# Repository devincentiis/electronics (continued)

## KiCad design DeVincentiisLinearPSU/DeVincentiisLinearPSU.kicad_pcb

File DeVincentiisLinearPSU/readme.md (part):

DIGITAL LINEAR POWER SUPPLY
=====================================

**PROJECT DESCRIPTION**

Electronics enthusiasts who want to try their hand at self-building a digital linear power supply for a small laboratory can create this device which in a single PCB brings together the essential functions to have a truly useful instrument.  
Taking inspiration from some circuit solutions of linear power supplies created in the past and available on the internet, this digitized model was conceived with microcontroller, DAC, LCD display and a single rotary encoder for interaction with the user.  
The objective is to be used with double winding 12-24 Vac transformers and a power of up to approximately 80VA capable of generating output voltages from 0 to 24 volts and currents from 0 to 3 amperes.  
With appropriate modifications the circuit could be scaled in both current and voltage. As it is it also accepts transformers with slightly different voltages, for example 15-30 or 10-20 Vac. At boot, the voltage supplied by the transformer is checked to set the maximum selectable via the rotary encoder and the possible presence of an intermediate socket.  
The power supply and the program also allow the use of single output transformers, at start-up the lack of the central socket is detected and indicated on the display and everything will continue to function regularly, however, it must be kept in mind that when we ask for supplies with high currents at low voltages, the two power transistors will have to dissipate a lot of heat and will force us to equip them with important heat sinks for cooling with forced ventilation.  
With a double winding transformer, however, the problem is halved as below the median voltage (also detected at switch-on) the relay will automatically switch to draw energy from the central tap of the transformer.  
The performance will never be the same as a modern switching power supply, but it will not be noisy. As you know, the operating principle is several decades old but is still considered valid in the laboratory where it is more likely to have problems with noise rather than heat.  
It can also be seen as a circuit to be connected to a transformer that has been in stock for many years and has never been used. In **Picture1** you can see one of the first creation placed into old media-center enclosure.

The firmware and wiring diagram are open source so they can be modified, resized, patched.  
An important improvement would be to replace the micro with an [STM32](http://www.st.com/en/microcontrollers-microprocessors/stm32f103ze.html) in the versions with two 12bit DACs, the considerable computing power would also [allow it to manage a touch display](https://github.com/ag88/Adafruit_ILI9341_SPI_stm32duino).  
Conversely, those who are used to Arduino Uno, Nano, etc. could replace the digital stage by adding another external DAC or replacing the current one with a two-channel one to control the analog stage.  
The presence of the I2C plug allows many expansions, for example by moving the LCD display onto it and equipping it with a PCF8574 module and using the [appropriate library for ATtiny](https://github.com/fdebrabander/Arduino-LiquidCrystal-I2C-library), thus leaving several pins free and if you have a transformer with more intermediate headers on the secondary it would be enough to modify the program to do so so that more steps of voltages can be chosen ( wiring diagram in **[Picture 3](https://github.com/devincentiis/electronics/blob/main/DeVincentiisLinearPSU/picture3.jpg)** ). If you want to do without the digital part while maintaining the switching of the transformer voltage, the circuit is simplified and you can base it on this: [**Analog schematic**](https://github.com/devincentiis/electronics/blob/main/DeVincentiisLinearPSU/AnalogLinearPSU.pdf)**.** Electronics maker often also have a 3D printer: they can have fun designing the front panel, the case and whatever else is necessary. The circuit uses the low voltage coming from the secondary of a transformer but any educational use on both the hardware and software side must be carried out under the **guidance of qualified and competent teachers who assume responsibility.**

**DECLARATION OF RESPONSIBILITY**

**The author therefore assumes NO RESPONSIBILITY** in civil or criminal matters and does not offer any implicit or explicit guarantee, and is not responsible for problems of any kind, damages or accidents deriving from the use of the information found on this web page , as well as from the use of the page itself or part of it. **Anyone who creates and/or uses modifications, diagrams, electrical circuits**, or mechanical parts or electronic theory information described here, **does so as their own free choice, assuming all responsibilities that may derive from them**, and will therefore not be able to claim any form of compensation from the author, in case of damage or accidents for everything described and said. In light of the above and **in consideration of the danger of electrocution deriving from the connection of the transformer primary**, the description on this project has been deliberately omitted and **remains the responsibility of qualified personnel in the electrical/electronic sector**.

**ELECTRONIC SCHEMATIC - CIRCUIT DIAGRAM**

**BILL OF MATERIALS - BOM**

| Reference                                  | Qty | Value                                                                             | Footprint                                     | DNP    |
|--------------------------------------------|-----|-----------------------------------------------------------------------------------|-----------------------------------------------|--------|
| C1, C2                                     | 2   | 47u 63V                                                                           | Capacitor_THT:CP_Radial_D6.3mm_P2.50mm        | &nbsp; |
| C3, C6, C11, C13, C16, C21, C23, C27       | 8   | 100n                                                                              | Capacitor_SMD:C_1206                          | &nbsp; |
| C4, C10, C12                               | 3   | 470n                                                                              | Capacitor_SMD:C_1206                          | &nbsp; |
| C5, C7                                     | 2   | 2200u 63V                                                                         | Capacitor_THT:CP_Radial_D18.0mm_P7.50mm       | &nbsp; |
| C8                                         | 1   | 47u 16V                                                                           | Capacitor_THT:CP_Radial_D5.0mm_P2.50mm        | &nbsp; |
| C9                                         | 1   | 1000u 35V                                                                         | Capacitor_THT:CP_Radial_D12.5mm_P5.00mm       | &nbsp; |
| C14                                        | 1   | 10u 50V                                                                           | Capacitor_THT:CP_Radial_D5.0mm_P2.50mm        | &nbsp; |
| C15                                        | 1   | 330p                                                                              | Capacitor_SMD:C_1206                          | &nbsp; |
| C17                                        | 1   | 1000u 10V                                                                         | Capacitor_THT:CP_Radial_D8.0mm_P3.50mm        | &nbsp; |
| C18, C22                                   | 2   | 10n                                                                              | Capacitor_SMD:C_1206                          | &nbsp; |
| C25                                        | 1   | 47u 35V                                                                           | Capacitor_THT:CP_Radial_D6.3mm_P2.50mm        | &nbsp; |
| C26                                        | 1   | 470u 63V                                                                          | Capacitor_THT:CP_Radial_D12.5mm_P5.00mm       | &nbsp; |
| D1, D3, D6, D8, D12                        | 5   | 1N4148                                                                            | Diode_SMD                                     | &nbsp; |
| D2                                         | 1   | 15V                                                                               | Diode_SMD                                     | &nbsp; |
| D4                                         | 1   | 100V 10A                                                                          | Diode_THT:Diode_Bridge_Vishay_KBL             | &nbsp; |
| D5                                         | 1   | SR5100                                                                            | Diode_THT:D_DO-201AD_P15.24mm_Horizontal      | &nbsp; |
| D9, D14                                    | 2   | 12V 1W                                                                            | Diode_SMD                                     | &nbsp; |
| D10                                        | 1   | LED                                                                               | LED_THT:LED_D3.0mm_Green                      | &nbsp; |
| D11                                        | 1   | LED                                                                               | LED_THT:LED_D3.0mm_Red                    | &nbsp; |
| D15                                        | 1   | 3.0V                                                                              | Diode_SMD:D_MiniMELF                          | &nbsp; |
| D16                                        | 1   | 1N4004                                                                            | Diode_SMD                                     | &nbsp; |
| DS1                                        | 1   | WC1602A                                                                           | Display:WC1602A                               | &nbsp; |
| J1                                         | 1   | 0-12-24Vac                                                                        | Connector 7,62_1x03_P7.62mm_Vertical          | &nbsp; |
| J2                                         | 1   | UPDI                                                                              | Connector PinHeader_1x03_P2.54mm_Vertical     | &nbsp; |
| J3                                         | 1   | 0-24V                                                                             | Connector 7,62_1x02_P7.62mm_Vertical          | &nbsp; |
| J4                                         | 1   | Fan 24V                                                                           | Connector PinHeader_1x02_P2.54mm_Vertical     | &nbsp; |
| J5                                         | 1   | +POW                                                                              | Faston:Faston                                 | &nbsp; |
| J6                                         | 1   | TP1                                                                               | Oscilloscope Test Point (ref-Vout)            | &nbsp; |
| J7                                         | 1   | +OUT                                                                              | Faston:FastonNoCourt                          | &nbsp; |
| J8                                         | 1   | -POW                                                                              | Faston:Faston                                 | &nbsp; |
| J9                                         | 1   | I2Csocket                                                                         | Connector PinHeader_1x04_P2.54mm_Vertical     | &nbsp; |
| K1                                         | 1   | RELAY                                                                             | Relay_THT:Relay_SPDT_24V=            | &nbsp; |
| L1                                         | 1   | 3A 22uH 75mΩ                                                                      | Inductor_THT: D9.5mm_P5.00mm    | &nbsp; |
| Q1                                         | 1   | BC817                                                                             | Package_TO_SOT_SMD:SOT-23                     | &nbsp; |
| Q2                                         | 1   | BD139                                                                             | Package THT:TO-126-3_Vertical                 | &nbsp; |
| Q3                                         | 1   | BC857                                                                             | Package SMD:SOT-23                            | &nbsp; |
| Q4                                         | 1   | TIP126                                                                            | Package THT:TO-220-3_Vertical                 | &nbsp; |
| Q5, Q8, Q10                                | 3   | BC846                                                                             | Package SMD:SOT-23                            | &nbsp; |
| Q6, Q7                                     | 2   | TIP3055                                                                           | Package THT:TO-247-3_Vertical                 | &nbsp; |
| Q9                                         | 1   | MMBTA06                                                                           | Package SMD:SOT-23                            | &nbsp; |
| R1                                         | 1   | 82                                                                                | Resistor_THT: L14.3mm_D5.7mm_P7.62mm_Vertical | &nbsp; |
| R2, R4, R40                                | 3   | 390                                                                               | Resistor_SMD:R_1206                           | &nbsp; |
| R3                                         | 1   | 270                                                                               | Resistor_SMD:R_1206                           | &nbsp; |
| R5                                         | 1   | 1000                                                                              | Resistor_SMD:R_2512                           | &nbsp; |
| R6                                         | 1   | 56K                                                                               | Resistor_SMD:R_1206                           | &nbsp; |
| R7, R11, R21, R33, R34, R36, R39, R45, R46 | 9   | 4700                                                                              | Resistor_SMD:R_1206                           | &nbsp; |
| R8, R13, R15, R18, R48                     | 5   | 1500                                                                              | Resistor_SMD:R_1206                           | &nbsp; |
| R9, R14, R17, R35                          | 4   | 10K                                                                               | Resistor_SMD:R_1206                           | &nbsp; |
| R10                                        | 1   | 15K                                                                               | Resistor_SMD:R_1206                           | &nbsp; |
| R12                                        | 1   | 0.47                                                                              | Resistor_THT: L25.0mm_W9.0mm_P27.94mm         | &nbsp; |
| R16                                        | 1   | 2200                                                                              | Resistor_SMD:R_1206                           | &nbsp; |
| R20, R23                                   | 2   | 22K                                                                               | Resistor_SMD:R_1206                           | &nbsp; |
| R19, R43, R44, R50, R51                    | 5   | 1000                                                                              | Resistor_SMD:R_1206                           | &nbsp; |
| R24, R25, R26, R27, R37                    | 5   | 2700                                                                              | Resistor_SMD:R_1206                           | &nbsp; |
| R28                                        | 1   | 47K                                                                               | Resistor_SMD:R_1206                           | &nbsp; |
| R29, R30                                   | 2   | 0.22                                                                              | Resistor_THT: L14.3mm_D5.7mm_P20.32mm         | &nbsp; |
| R31, R42                                   | 2   | 47                                                                                | Resistor_SMD:R_2512                           | &nbsp; |
| R32                                        | 1   | 33K                                                                               | Resistor_SMD:R_1206                           | &nbsp; |
| R41                                        | 1   | 390                                                                               | Resistor_SMD:R_2512                           | &nbsp; |
| R49                                        | 1   | 150K                                                                              | Resistor_SMD:R_1206                           | &nbsp; |
| RV1                                        | 1   | 5K                                                                                | Potentiometer 3296W_Vertical                  | &nbsp; |
| RV2, RV5, RV6                              | 3   | 100K                                                                              | Potentiometer 3296W_Vertical                  | &nbsp; |
| RV3, RV4                                   | 2   | 10K                                                                               | Potentiometer 3296W_Vertical                  | &nbsp; |
| SW1                                        | 1   | EC11                                                                              | Connector PinHeader_1x05_P2.54mm_Vertical     | &nbsp; |
| U2, U5, U7                                 | 3   | TL081                                                                             | Package_SO:SOIC-8_3.9x4.9mm_P1.27mm           | &nbsp; |
| U3                                         | 1   | LM337L_SO8                                                                        | Package_SO:SOIC-8_3.9x4.9mm_P1.27mm           | &nbsp; |
| U4                                         | 1   | L7805                                                                             | Package THT:TO-220-3_Vertical                 | &nbsp; |
| U6                                         | 1   | ATtiny3216-S                                                                      | Package_SO:SOIC-20W_7.5x12.8mm_P1.27mm        | &nbsp; |
| U8                                         | 1   | MCP4725                                                                           | Package SMD:SOT-23-6                          | &nbsp; |

**CIRCUIT DIAGRAM DESCRIPTION**

The alternating current coming from the double winding transformer 24-12 (or 30-15) enters J1, 0-24 Vac goes directly to the diode bridge D4 while the central one passes through D5 and rectify only the positive half-waves that arrive alternately from side 24 or from the 0 side; therefore when the relay is energized and therefore we are using half power the rectification using only half the diode bridge (- side) and the D5 diode, at full power it works in the classic way with only the full bridge. Regardless of the voltage chosen by the relay it will charge the smoothing capacitors C5, C7.  
D16 prevents that when the relay switches from 12 to 24 the charge present on C26 flows onto the smoothing capacitors with a high current, tending to "stick" the relay contacts, especially if they are of poor quality.  
The branch that passes through R1, C1, C2, C3, D1, D2, D3 is used to obtain a negative voltage of 3.1V for the operational amplifiers U2, U5, U7 in order to allow them to bring the output to 0V compared to PWRGND; it is an old and well-known circuit solution which has also been stabilized with an [LM337](https://www.ti.com/product/LM337L). Here the fictitious resistor is not needed to always keep the diode bridge under load in order to generate voltage on the negative branch as the function takes care of the absorption due to the power supply of the integrated circuits. The 24 volts are obtained with a [BD139](https://www.st.com/en/power-transistors/bd139.html) (Q2) coupled to the zeners and which supports input voltages up to 80V compared to the 40V of a possible 7824, the R42 resistor prevents the peak current at start-up from exceeding the maximum collector of the transistor , therefore the 24V line serves the operational amplifiers, the relay, the fan (60mA or more if we cool Q2 well) then continues towards the regulator for the 5V of the digital circuits U6, U8, display. Due to the fact that when the device is turned off the relay would vibrate dangerously because both the leveling capacitors C5-C7 and C17 remain charged, and therefore the microcontroller U6 served by it, it was necessary Q10 an NPN BJT which goes into conduction only during shutdown, it has the same behavior as Q8 (which we will see later) but it is used to communicate to the microcontroller not to turn the relay back on to use HALF\_PWR even if the output voltage is below half as the shutdown is in progress.  
The digital stage is based on U6, a suitably programmed [ATtiny3216](https://www.microchip.com/en-us/product/attiny3216) microcontroller; it is the heart of the entire system and represents the distinctive feature of this linear power supply. Let's analyze it starting from the analog inputs and outputs to and from the control operational amplifiers.  
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
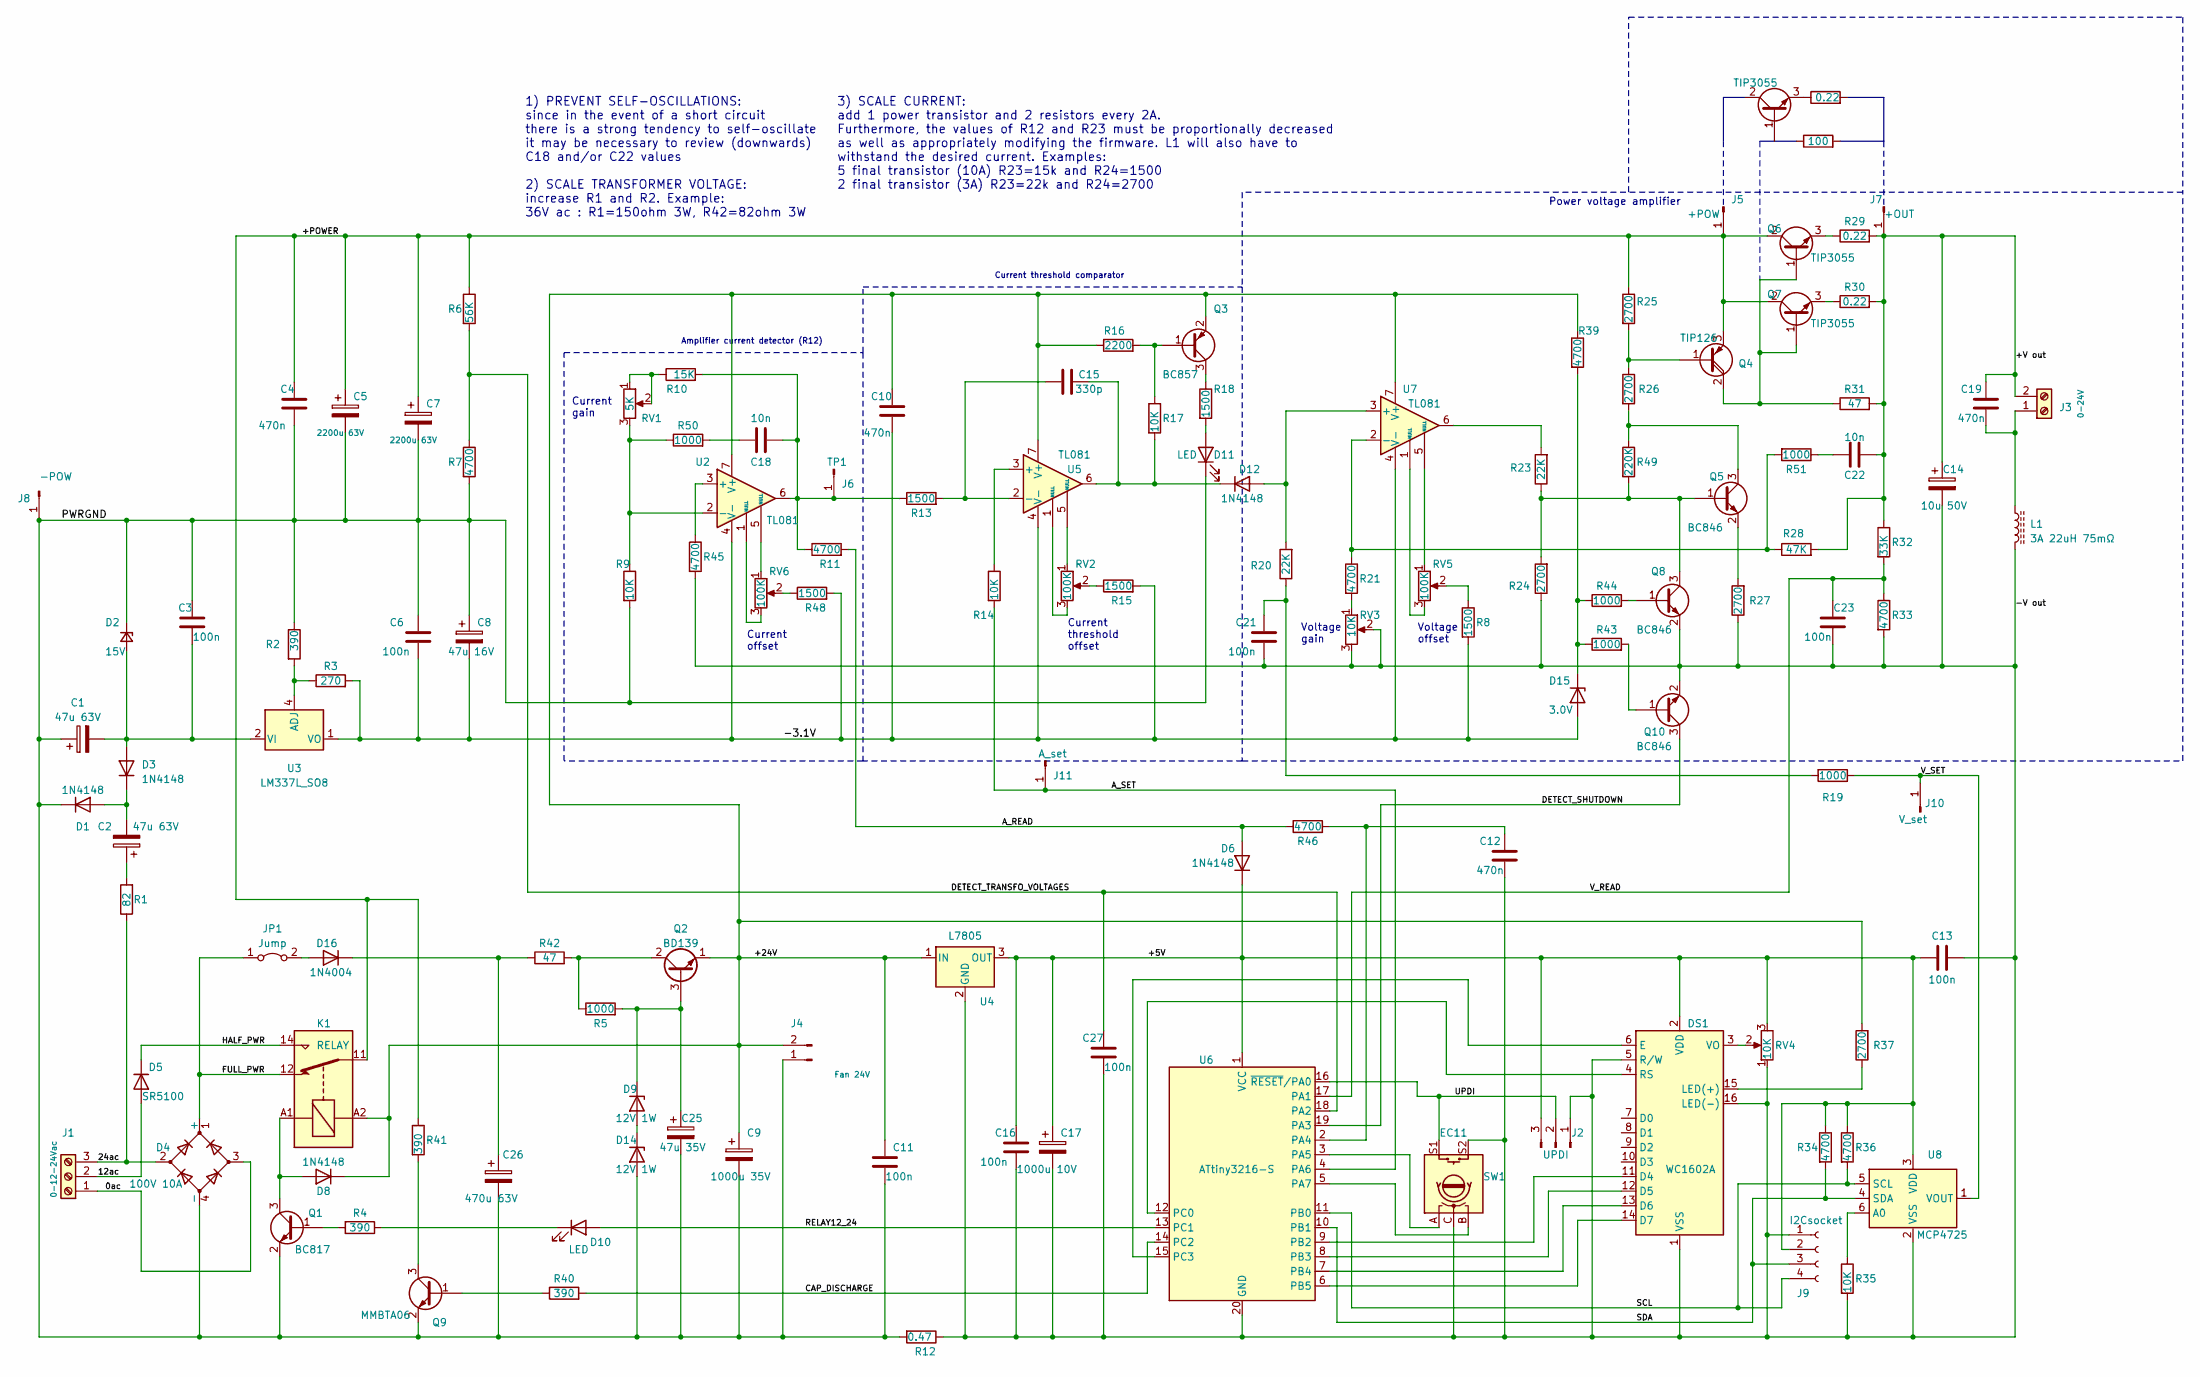
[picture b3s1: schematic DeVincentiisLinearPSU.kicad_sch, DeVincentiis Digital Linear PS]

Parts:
C1, C2: 47u 63V; CP_Radial_D6.3mm_P2.50mm
C3, C6, C11, C13, C16, C21, C23, C27: 100n; C_1206_3216Metric_Pad1.33x1.80mm_HandSolder
C4, C10, C12, C19: 470n; C_1206_3216Metric_Pad1.33x1.80mm_HandSolder
C5, C7: 2200u 63V; CP_Radial_D18.0mm_P7.50mm
C8: 47u 16V; CP_Radial_D5.0mm_P2.50mm
C9: 1000u 35V; CP_Radial_D12.5mm_P5.00mm
C14: 10u 50V; CP_Radial_D5.0mm_P2.50mm
C15: 330p; C_1206_3216Metric_Pad1.33x1.80mm_HandSolder
C17: 1000u 10V; CP_Radial_D8.0mm_P3.50mm
C18, C22: 10n; C_1206_3216Metric_Pad1.33x1.80mm_HandSolder
C25: 47u 35V; CP_Radial_D6.3mm_P2.50mm
C26: 470u 63V; CP_Radial_D12.5mm_P5.00mm
D1, D3, D6, D8, D12: 1N4148; D_SMA
D2: 15V; D_SMA
D4: 100V 10A; Diode_Bridge_Vishay_KBL
D5: SR5100; D_DO-201AD_P15.24mm_Horizontal
D9, D14: 12V 1W; D_SMA
D10: LED; LED_D3.0mm_Clear
D11: LED; LED_D3.0mm_FlatTop
D15: 3.0V; D_MiniMELF
D16: 1N4004; D_SMA
DS1: WC1602A
J1: 0-12-24Vac; PhoenixContact_GMSTBVA_2,5_3-G-7,62_1x03_P7.62mm_Vertical
J2: UPDI; PinHeader_1x03_P2.54mm_Vertical
J3: 0-24V; PhoenixContact_GMSTBVA_2,5_2-G-7,62_1x02_P7.62mm_Vertical
J4: Fan 24V; PinHeader_1x02_P2.54mm_Vertical
J5: +POW; Faston
J6: TP1; PinHeader_1x01_P2.54mm_Vertical
J7: +OUT; FastonNoCourt
J8: -POW; Faston
J9: I2Csocket; PinHeader_1x04_P2.54mm_Vertical
J10: V_set; PinHeader_1x01_P2.54mm_Vertical
J11: A_set; PinHeader_1x01_P2.54mm_Vertical
JP1: Jump; PinHeader_1x02_P2.54mm_Vertical
K1: RELAY; Relay_SPDT_Finder_36.11
L1: 3A 22uH 75mΩ; L_Radial_D9.5mm_P5.00mm_Fastron_07HVP
Q1: BC817; SOT-23
Q2: BD139; TO-126-3_Vertical
Q3: BC857; SOT-23
Q4: TIP126; TO-220-3_Vertical
Q5, Q8, Q10: BC846; SOT-23
Q6, Q7: TIP3055; TO-247-3_Vertical
Q9: MMBTA06; SOT-23
Q11: TIP3055; TO-218-3_Vertical
R1: 82; R_Axial_DIN0614_L14.3mm_D5.7mm_P7.62mm_Vertical
R2, R4, R40: 390; R_1206_3216Metric_Pad1.30x1.75mm_HandSolder
R3: 270; R_1206_3216Metric_Pad1.30x1.75mm_HandSolder
R5: 1000; R_2512_6332Metric_Pad1.40x3.35mm_HandSolder
R6: 56K; R_1206_3216Metric_Pad1.30x1.75mm_HandSolder
R7, R11, R21, R33, R34, R36, R39, R45, R46: 4700; R_1206_3216Metric_Pad1.30x1.75mm_HandSolder
R8, R13, R15, R18, R48: 1500; R_1206_3216Metric_Pad1.30x1.75mm_HandSolder
R9, R14, R17, R35: 10K; R_1206_3216Metric_Pad1.30x1.75mm_HandSolder
R10: 15K; R_1206_3216Metric_Pad1.30x1.75mm_HandSolder
R12: 0.47; R_Axial_Power_L25.0mm_W9.0mm_P27.94mm
R16: 2200; R_1206_3216Metric_Pad1.30x1.75mm_HandSolder
R19, R43, R44, R50, R51: 1000; R_1206_3216Metric_Pad1.30x1.75mm_HandSolder
R20, R23: 22K; R_1206_3216Metric_Pad1.30x1.75mm_HandSolder
R24, R25, R26, R27, R37: 2700; R_1206_3216Metric_Pad1.30x1.75mm_HandSolder
R28: 47K; R_1206_3216Metric_Pad1.30x1.75mm_HandSolder
R29, R30: 0.22; R_Axial_DIN0614_L14.3mm_D5.7mm_P20.32mm_Horizontal
R31, R42: 47; R_2512_6332Metric_Pad1.40x3.35mm_HandSolder
R32: 33K; R_1206_3216Metric_Pad1.30x1.75mm_HandSolder
R38: 0.22
R41: 390; R_2512_6332Metric_Pad1.40x3.35mm_HandSolder
R47: 100
R49: 220K; R_1206_3216Metric_Pad1.30x1.75mm_HandSolder
RV1: 5K; Potentiometer_Bourns_3296W_Vertical
RV2, RV5, RV6: 100K; Potentiometer_Bourns_3296W_Vertical
RV3, RV4: 10K; Potentiometer_Bourns_3296W_Vertical
SW1: EC11; PinHeader_1x05_P2.54mm_Vertical
U2, U5, U7: TL081; SOIC-8_3.9x4.9mm_P1.27mm
U3: LM337L_SO8; SOIC-8_3.9x4.9mm_P1.27mm
U4: L7805; TO-220-3_Vertical
U6: ATtiny3216-S; SOIC-20W_7.5x12.8mm_P1.27mm
U8: MCP4725; SOT-23-6

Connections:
/0ac: D4.3, J1.1
/12ac: D5.2 (A), J1.2
/24ac: D4.2, J1.3, R1.1
/+5V: C13.1, C16.1, C17.1, D6.1 (K), DS1.2 (VDD), J2.3, J9.2, R34.1, R36.1, RV4.3, U4.3 (OUT), U6.1 (VCC), U8.3 (VDD)
/+24V: C9.1, C10.1, C11.1, D8.1 (K), J4.2, K1.A2, Q2.1 (E), Q3.2 (E), R16.1, R37.2, R39.1, U2.7 (V+), U4.1 (IN), U5.7 (V+), U7.7 (V+)
/+POWER: C4.1, C5.1, C7.1, J5.1, K1.11, Q4.3 (E), Q6.2 (C), Q7.2 (C), R6.1, R25.1, R41.1
/+V out: C14.1, C19.1, C22.1, J3.2, J7.1, R28.2, R29.2, R30.2, R31.2, R32.1
/-3.1V: C6.2, C8.2, C10.2, D15.2 (A), R3.2, R8.2, R15.2, R48.2, U2.4 (V-), U3.1 (VO), U5.4 (V-), U7.4 (V-)
/-V out: C12.2, C13.2, C14.2, C16.2, C17.2, C21.2, C23.2, C27.2, DS1.1 (VSS), DS1.5 (R/W), DS1.16 (LED(-)), J2.1, J9.1, L1.2, Q8.2 (E), Q10.2 (E), R12.1, R24.1, R27.1, R33.2, R35.2, R45.2, RV3.2, RV3.3, RV4.1, SW1.C, SW1.S2, U4.2 (GND), U6.20 (GND), U8.2 (VSS)
/A_READ: D6.2 (A), R11.2, R46.1
/A_SET: J11.1, R14.2, U6.4 (PA6)
/CAP_DISCHARGE: R40.2, U6.14 (PC2)
/DETECT_SHUTDOWN: Q10.3 (C), U6.19 (PA3)
/DETECT_TRANSFO_VOLTAGES: C27.1, R6.2, R7.1, U6.18 (PA2)
/FULL_PWR: D4.1 (+), JP1.1 (A), K1.12
/HALF_PWR: D5.1 (K), K1.14
/PWRGND: C1.1, C3.1, C4.2, C5.2, C6.1, C7.2, C8.1, C9.2, C11.2, C25.2, C26.2, D1.1 (K), D2.1 (K), D4.4 (-), D11.1 (K), D14.2 (A), J4.1, J8.1, Q1.2 (E), Q9.2 (E), R2.1, R7.2, R9.2, R12.2
/RELAY12_24: D10.2 (A), U6.13 (PC1)
/SCL: J9.4, R36.2, U6.11 (PB0), U8.5 (SCL)
/SDA: J9.3, R34.2, U6.10 (PB1), U8.4 (SDA)
/UPDI: J2.2, SW1.S1, U6.16 (~RESET/PA0)
/V_READ: C23.1, R32.2, R33.1, U6.17 (PA1)
/V_SET: J10.1, R19.1, U8.1 (VOUT)
unnamed: C2.1, R1.2
unnamed: C18.1, R50.2
unnamed: C21.1, R19.2, R20.1
unnamed: C22.2, R51.1
unnamed: C2.2, D1.2 (A), D3.1 (K)
unnamed: C1.2, C3.2, D2.2 (A), D3.2 (A), U3.2 (VI), U3.3 (VI), U3.6 (VI), U3.7 (VI)
unnamed: D8.2 (A), K1.A1, Q1.3 (C)
unnamed: C25.1, D9.1 (K), Q2.3 (B), R5.2
unnamed: D10.1 (K), R4.1
unnamed: D11.2 (A), R18.2
unnamed: D12.2 (A), R20.2, U7.3 (+)
unnamed: C15.2, D12.1 (K), R17.2, U5.6
unnamed: D9.2 (A), D14.1 (K)
unnamed: D15.1 (K), R39.2, R43.1, R44.1
unnamed: D16.2 (A), JP1.2 (B)
unnamed: C26.1, D16.1 (K), R42.1
unnamed: DS1.11 (D4), U6.9 (PB2)
unnamed: DS1.12 (D5), U6.8 (PB3)
unnamed: DS1.13 (D6), U6.7 (PB4)
unnamed: DS1.14 (D7), U6.6 (PB5)
unnamed: DS1.6 (E), U6.15 (PC3)
unnamed: DS1.15 (LED(+)), R37.1
unnamed: DS1.4 (RS), U6.12 (PC0)
unnamed: DS1.3 (VO), RV4.2
unnamed: C19.2, J3.1, L1.1
unnamed: C18.2, J6.1, R10.2, R11.1, R13.1, U2.6
unnamed: Q1.1 (B), R4.2
unnamed: Q2.2 (C), R5.1, R42.2
unnamed: Q3.1 (B), R16.2, R17.1
unnamed: Q3.3 (C), R18.1
unnamed: Q4.1 (B), R25.2, R26.1
unnamed: Q4.2 (C), Q6.1 (B), Q7.1 (B), R31.1
unnamed: Q5.1 (B), Q8.3 (C), R23.1, R24.2, R49.2
unnamed: Q5.3 (C), R26.2, R49.1
unnamed: Q5.2 (E), R27.2
unnamed: Q6.3 (E), R29.1
unnamed: Q7.3 (E), R30.1
unnamed: Q8.1 (B), R44.2
unnamed: Q9.1 (B), R40.1
unnamed: Q9.3 (C), R41.2
unnamed: Q10.1 (B), R43.2
unnamed: Q11.3 (E), R38.1
unnamed: R8.1, RV5.2
unnamed: R10.1, RV1.1, RV1.2
unnamed: R15.1, RV2.2
unnamed: R21.2, RV3.1
unnamed: R23.2, U7.6
unnamed: R48.1, RV6.2
unnamed: RV2.1, U5.5 (NULL)
unnamed: RV2.3, U5.1 (NULL)
unnamed: RV5.1, U7.5 (NULL)
unnamed: RV5.3, U7.1 (NULL)
unnamed: RV6.1, U2.5 (NULL)
unnamed: RV6.3, U2.1 (NULL)
unnamed: R45.1, U2.3 (+)
unnamed: R9.1, R50.1, RV1.3, U2.2 (-)
unnamed: R2.2, R3.1, U3.4 (ADJ)
unnamed: R14.1, U5.3 (+)
unnamed: C15.1, R13.2, U5.2 (-)
unnamed: C12.1, R46.2, U6.2 (PA4)
unnamed: SW1.A, U6.3 (PA5)
unnamed: SW1.B, U6.5 (PA7)
unnamed: R21.1, R28.1, R51.2, U7.2 (-)
unnamed: R35.1, U8.6 (A0)

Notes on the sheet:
Voltage offset
Current threshold comparator
Voltage gain
Current gain
Power voltage amplifier
Amplifier current detector (R12)
Current threshold offset
1) PREVENT SELF-OSCILLATIONS: since in the event of a short circuit there is a strong tendency to self-oscillate it may be necessary to review (downwards) C18 and/or C22 values 2) SCALE TRANSFORMER VOLTAGE: increase R1 and R2. Example: 36V ac : R1=150ohm 3W, R42=82ohm 3W
Current offset
3) SCALE CURRENT: add 1 power transistor and 2 resistors every 2A. Furthermore, the values of R12 and R23 must be proportionally decreased as well as appropriately modifying the firmware. L1 will also have to withstand the desired current. Examples: 5 final transistor (10A) R23=15k and R24=1500 2 f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

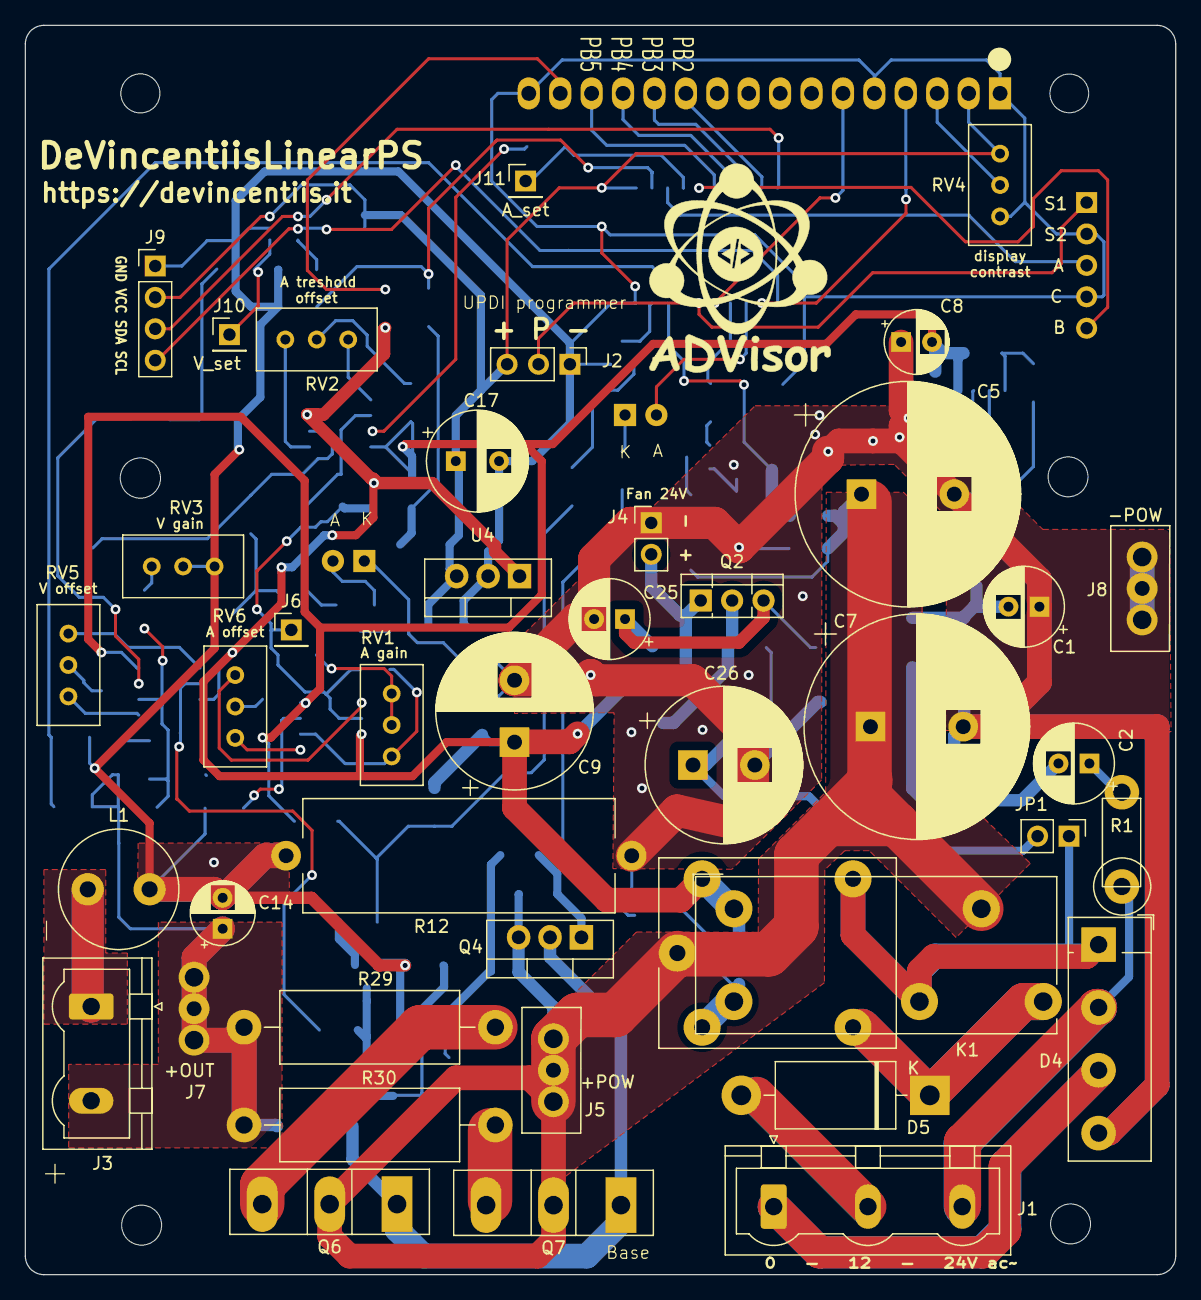
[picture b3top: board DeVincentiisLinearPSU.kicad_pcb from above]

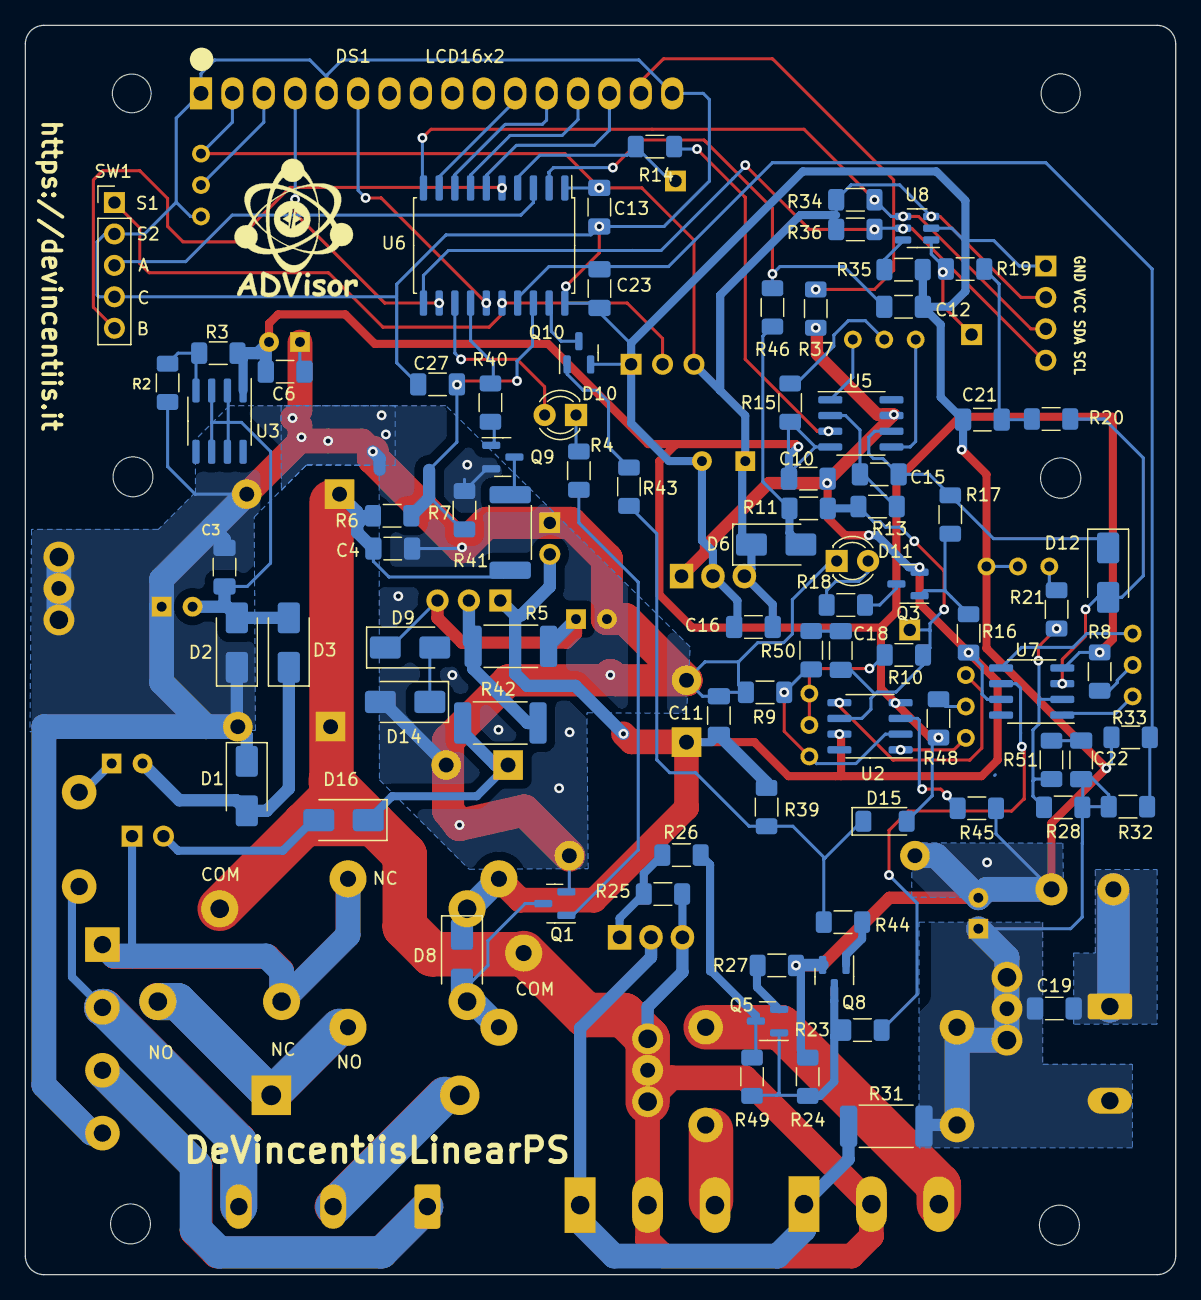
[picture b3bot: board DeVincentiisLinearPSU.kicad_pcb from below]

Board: 2 copper layers, 93.0 x 101.0 mm, 126 parts (85 on the bottom side), 86 nets.

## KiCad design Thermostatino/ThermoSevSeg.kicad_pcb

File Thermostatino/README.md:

# 3 Digit 7 Segment thermostat with K type thermocouple for Arduino Nano 

This is an Arduino Nano 3-digit 7-segment thermostat design with Kicad schematic diagram and PCB.
The firmware you find does not have the PID, you can have fun adding it according to your needs.

### Use instructions

* Select type of output combine UP, DOWN and FAN: push 3 seconds enconder switch
* Set temperature: turn the potentiometer (while viewing the set value)
* Set timer: turn the encoder (while viewing the set value)
* When timer turn to zero: OFF all 
* Without moving any knobs: display temperature

### Schematic and PCB EDA [KiCad](https://www.kicad.org/download/) 

### Firmware library for [Arduino IDE 1.8.19](https://github.com/arduino/Arduino) 

* SevSeg 3.7.0 by Dean Reading [Github Project Page](https://github.com/DeanIsMe/SevSeg/)
* Simple Rotary 1.1.3 by MPrograms [Github Project Page](https://github.com/mprograms/SimpleRotary/)
* MAX6675 1.1.0 by Adafruit [Github Project Page](https://github.com/adafruit/MAX6675-library/)

|Ref         |Qnty|Value|Cmp name         |Footprint                      |Description                                                                                    |
|------------|----|-----|-----------------|-------------------------------|-----------------------------------------------------------------------------------------------|
|A1,         |1   |Arduino_Nano_v3.x|Arduino_Nano_v3.x|Module:Arduino_Nano            |Arduino Nano v3.x                                                                              |
|C1, C4,     |2   |10u  |C_Polarized      |Capacitor_THT:CP_Radial_D6.3mm_P2.50mm|Polarized capacitor                                                                            |
|C2, C3,     |2   |100n |C_Small          |Capacitor_SMD:C_1206_3216Metric_Pad1.33x1.80mm_HandSolder|Unpolarized capacitor, small symbol                                                            |
|D1, D2, D5, |3   |LED  |LED              |LED_THT:LED_D5.0mm             |Light emitting diode                                                                           |
|D3, D4, D6, |3   |SS14 |D_Schottky       |Diode_SMD:D_SMA                |Schottky diode                                                                                 |
|J1,         |1   |Terminalx02|Screw_Terminal_01x02|TerminalBlock:TerminalBlock 02_P7.50mm_Horizontal|Generic screw terminal                                                                         |
|J2,         |1   |Terminalx05|Screw_Terminal_01x05|TerminalBlock:TerminalBlock 5_P5.08mm|Generic screw terminal                                                                         |
|Q1, Q2, Q3, |3   |BC817|BC817            |Package_TO_SOT_SMD:SOT-23      |0.8A Ic, 45V Vce, NPN Transistor, SOT-23                                                       |
|R1, R2, R3, |3   |150  |R                |Resistor_SMD:R_1206_3216Metric_Pad1.30x1.75mm_HandSolder|Resistor                                                                                       |
|R4, R5, R6, |3   |220  |R                |Resistor_SMD:R_1206_3216Metric_Pad1.30x1.75mm_HandSolder|Resistor                                                                                       |
|RV1,        |1   |10K  |R_Potentiometer  |Potentiometer_THT:RK09K_Single_Vertical|Potentiometer                                                                                  |
|SW1,        |1   |RotaryEncoder|RotaryEncoder_Switch|Rotary_Encoder:RotaryEncoder_and_Switch_Vertical|Rotary encoder, dual channel, incremental quadrate outputs, with switch                        |
|U1,         |1   |MAX6675|MAX6675     |Package_SO:SOIC-8_3.9x4.9mm_P1.27mm|Cold Junction K-type Termocouple Interface, SPI, SO8                                           |
|U3,         |1   |LTD040BUE-101A|LTD040BUE-101A      |Display3bit:LTD040BUE-101A     |3 digit 7 segment super bright red LED, common anode                                           |

### Video (old prototype)

## License

MIT License

Copyright (c) 2023 to present - Antonio de Vincentiis

Permission is hereby granted, free of charge, to any person obtaining a copy
of this software and associated documentation files (the "Software"), to deal
in the Software without restriction, including without limitation the rights
to use, copy, modify, merge, publish, distribute, sublicense, and/or sell
copies of the Software, and to permit persons to whom the Software is
furnished to do so, subject to the following conditions:

The above copyright notice and this permission notice shall be included in all
copies or substantial portions of the Software.

THE SOFTWARE IS PROVIDED "AS IS", WITHOUT WARRANTY OF ANY KIND, EXPRESS OR
IMPLIED, INCLUDING BUT NOT LIMITED TO THE WARRANTIES OF MERCHANTABILITY,
FITNESS FOR A PARTICULAR PURPOSE AND NONINFRINGEMENT. IN NO EVENT SHALL THE
AUTHORS OR COPYRIGHT HOLDERS BE LIABLE FOR ANY CLAIM, DAMAGES OR OTHER
LIABILITY, WHETHER IN AN ACTION OF CONTRACT, TORT OR OTHERWISE, ARISING FROM,
OUT OF OR IN CONNECTION WITH THE SOFTWARE OR THE USE OR OTHER DEALINGS IN THE
SOFTWARE.

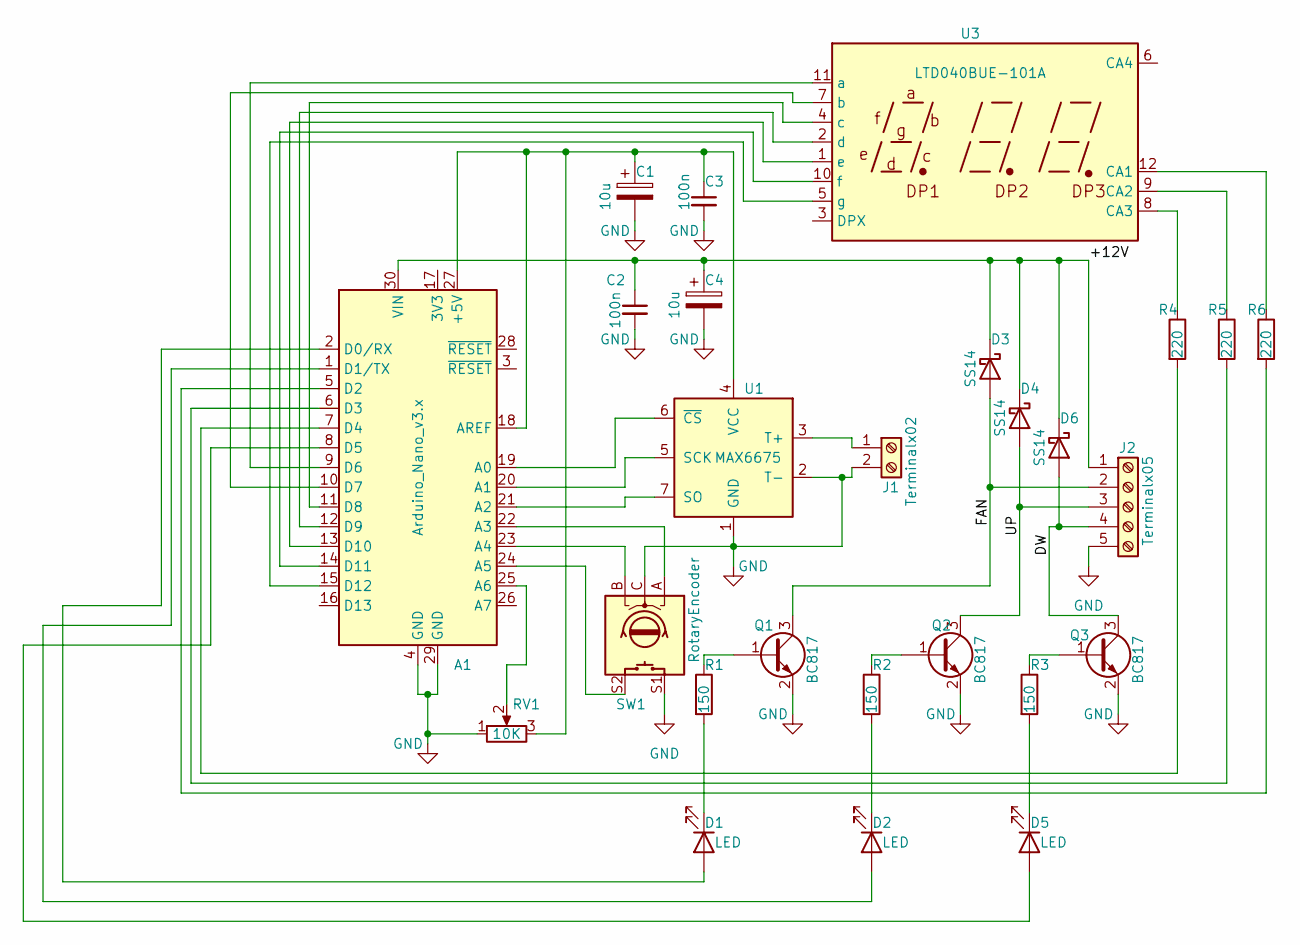
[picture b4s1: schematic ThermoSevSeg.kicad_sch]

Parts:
A1: Arduino_Nano_v3.x; Arduino_Nano
C1, C4: 10u; CP_Radial_D6.3mm_P2.50mm
C2, C3: 100n; C_1206_3216Metric_Pad1.33x1.80mm_HandSolder
D1, D2, D5: LED; LED_D5.0mm
D3, D4, D6: SS14; D_SMA
J1: Terminalx02; TerminalBlock_MetzConnect_Type171_RT13702HBWC_1x02_P7.50mm_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
J2: Terminalx05; TerminalBlock_bornier-5_P5.08mm
Q1, Q2, Q3: BC817; SOT-23
R1, R2, R3: 150; R_1206_3216Metric_Pad1.30x1.75mm_HandSolder
R4, R5, R6: 220; R_1206_3216Metric_Pad1.30x1.75mm_HandSolder
RV1: 10K; Potentiometer_Alps_RK09K_Single_Vertical
SW1: RotaryEncoder; RotaryEncoder_Alps_EC11E-Switch_Vertical_H20mm
U1: MAX6675; SOIC-8_3.9x4.9mm_P1.27mm
U3: LTD040BUE-101A

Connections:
/+12V: A1.30 (VIN), C2.1, C4.1, D3.1 (K), D4.1 (K), D6.1 (K), J2.1
/DW: D6.2 (A), J2.4, Q3.3 (C)
/FAN: D3.2 (A), J2.2, Q1.3 (C)
/UP: D4.2 (A), J2.3, Q2.3 (C)
GND: A1.4 (GND), A1.29 (GND), C1.2, C2.2, C3.2, C4.2, J1.2, J2.5, Q1.2 (E), Q2.2 (E), Q3.2 (E), RV1.1, SW1.C, SW1.S1, U1.1 (GND), U1.2 (T-)
unnamed: A1.1 (D1/TX), D2.2 (A)
unnamed: A1.2 (D0/RX), D1.2 (A)
unnamed: A1.5 (D2), R6.2
unnamed: A1.6 (D3), R5.2
unnamed: A1.7 (D4), R4.2
unnamed: A1.8 (D5), D5.2 (A)
unnamed: A1.9 (D6), U3.11 (a)
unnamed: A1.10 (D7), U3.7 (b)
unnamed: A1.11 (D8), U3.4 (c)
unnamed: A1.12 (D9), U3.2 (d)
unnamed: A1.13 (D10), U3.1 (e)
unnamed: A1.14 (D11), U3.10 (f)
unnamed: A1.15 (D12), U3.5 (g)
unnamed: A1.18 (AREF), A1.27 (+5V), C1.1, C3.1, RV1.3, U1.4 (VCC)
unnamed: A1.19 (A0), U1.6 (~CS)
unnamed: A1.20 (A1), U1.5 (SCK)
unnamed: A1.21 (A2), U1.7 (SO)
unnamed: A1.22 (A3), SW1.A
unnamed: A1.23 (A4), SW1.B
unnamed: A1.24 (A5), SW1.S2
unnamed: A1.25 (A6), RV1.2
unnamed: D1.1 (K), R1.2
unnamed: D2.1 (K), R2.2
unnamed: D5.1 (K), R3.2
unnamed: J1.1, U1.3 (T+)
unnamed: Q1.1 (B), R1.1
unnamed: Q2.1 (B), R2.1
unnamed: Q3.1 (B), R3.1
unnamed: R4.1, U3.8 (CA3)
unnamed: R5.1, U3.9 (CA2)
unnamed: R6.1, U3.12 (CA1)

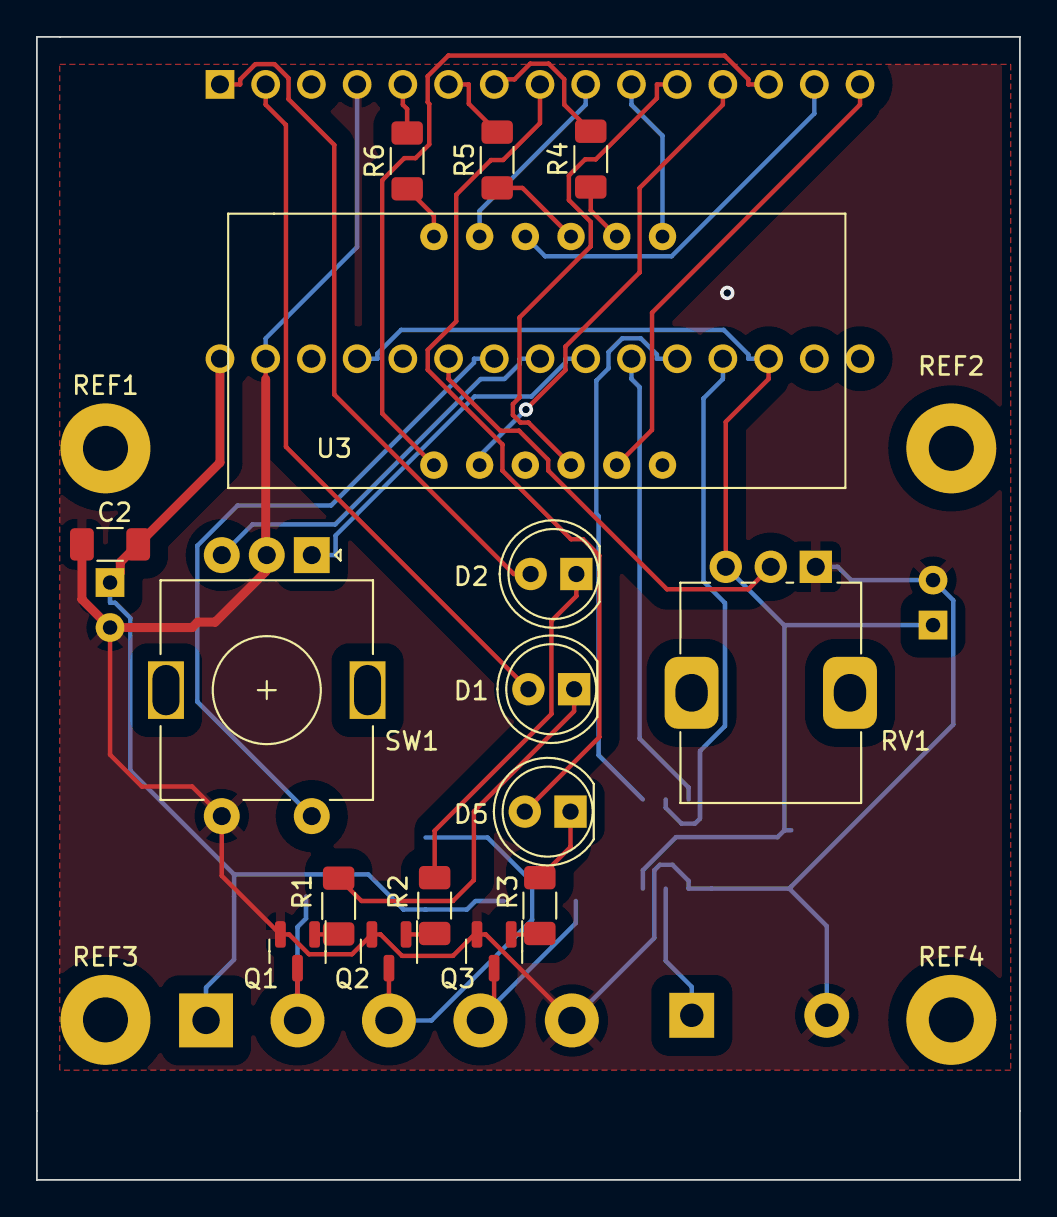
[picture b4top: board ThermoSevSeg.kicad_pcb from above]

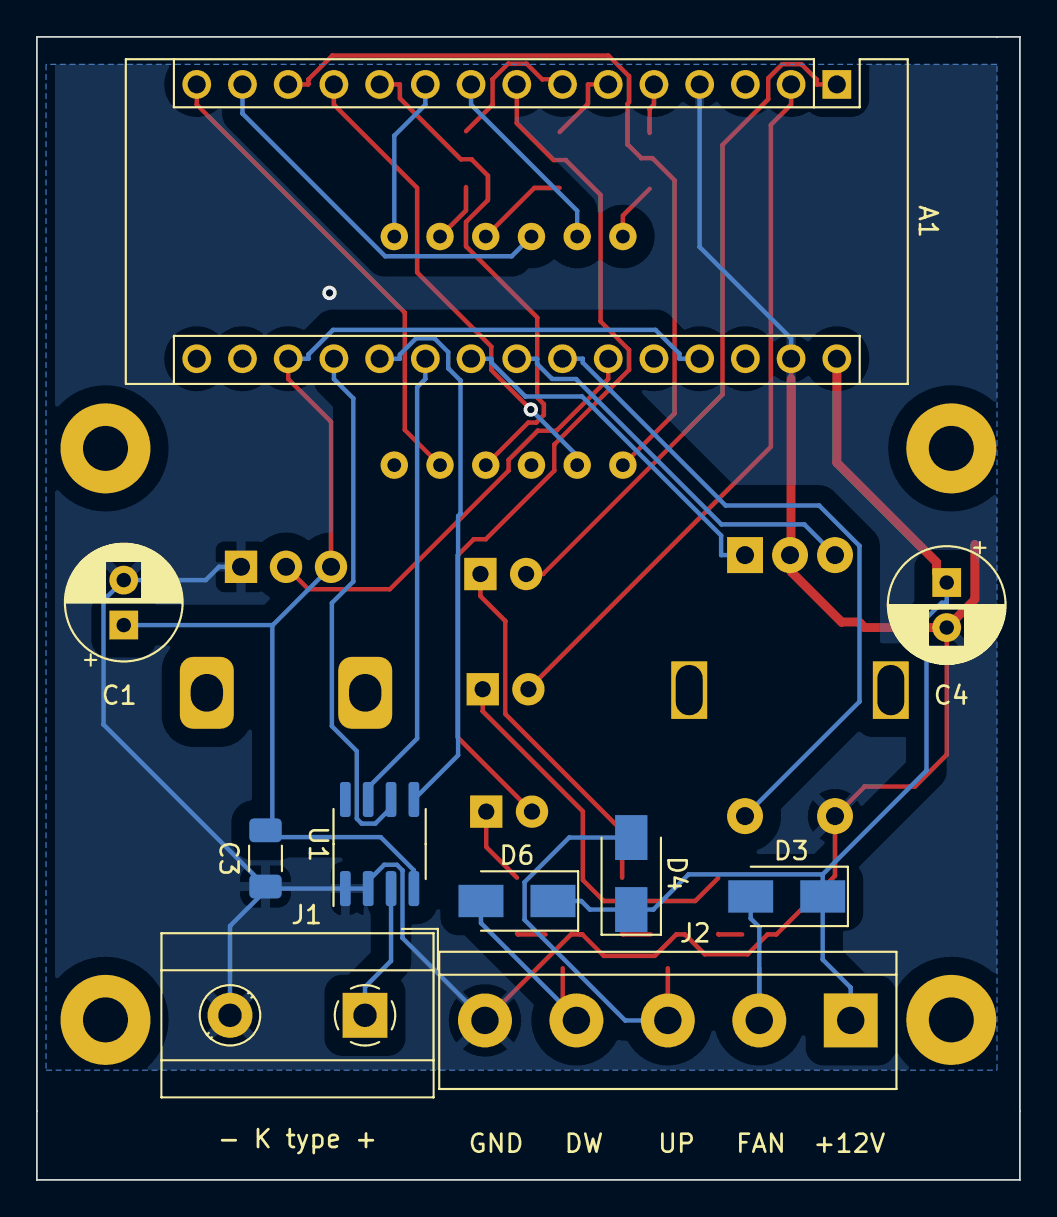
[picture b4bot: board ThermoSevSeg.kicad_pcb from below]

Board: 2 copper layers, 54.6 x 63.5 mm, 30 parts (10 on the bottom side), 36 nets.

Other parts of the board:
REF1, REF2, REF3, REF4: MountingHole_2.5mm_Pad

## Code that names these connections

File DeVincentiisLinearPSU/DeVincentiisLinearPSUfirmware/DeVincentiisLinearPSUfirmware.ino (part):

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#include "LiquidCrystal.h"
#include "EEPROM.h"

#define ROT_A PIN_PA5                   // (PA5) pin 3  from Rotary switch A pin
#define ROT_B PIN_PA7                   // (PA7) pin 5  from Rotary switch B pin
#define ROT_S PIN_PA0                   // (PA0) pin 16 from Rotary Button pin
#define CAP_DISCHARGE PIN_PC2           // (PC2) pin 14 to transistor for pulldown of the smoothing capacitors at bootstrap
#define V_READ PIN_PA1                  // (PA1) pin 17 from output voltage resistor net
#define DETECT_TRANSFO_VOLTAGE PIN_PA2  // (PA2) pin 18 from smoothing capacitors resistor net voltage detect
#define DETECT_SHUTDOWN PIN_PA3         // (PA3) pin 19 from transistor for detect when line -3,1V flotting (at shutdown)
#define A_READ PIN_PA4                  // (PA4) pin 2  from output current detector opamp 
#define A_SET PIN_PA6                   // (PA6) pin 4  to set max current 
#define RELAY12_24 PIN_PC1              // (PC1) pin 13 to relay driver transistor

unsigned long timer_decisec = millis();
int current_decisec = 0;
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  // INTERNAL DAC
  DACReference(INTERNAL4V3);
  analogReference(INTERNAL4V3); // ADC read real voltage and current
  pinMode(A_SET,OUTPUT); // DAC output to PA6

  //OTHER
  pinMode(RELAY12_24,OUTPUT); 
  pinMode(CAP_DISCHARGE,OUTPUT); 
  digitalWrite(RELAY12_24, HIGH); // startup at 12Vac 

  // DETECT TRANSFORMER VOLTAGE 
  pinMode(DETECT_TRANSFO_VOLTAGE,INPUT);

  // DETECT SHOTDOWN
  pinMode(DETECT_SHUTDOWN,INPUT_PULLUP);

  // ROTARY ENCODE
  pinMode(ROT_A,INPUT_PULLUP);
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
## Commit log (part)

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2023-03-20 license
2023-03-20 add images
2023-03-20 added 3d views
2023-03-20 added schematic
2023-03-22 update to kicad7
2023-03-22 update board and schema
2023-03-22 EDA version
2023-03-22 refuse
2023-03-22 embedded video
2023-03-23 update description
2023-03-24 update display
2024-06-26 vscode workspace
2024-08-03 moved to subdir
2024-08-03 init main readme
2024-08-03 update adn review
2024-08-03 update gitignore
2024-08-03 remove prl
2024-08-05 init project Water Flush Muse
2024-08-05 init project
2024-08-05 initi
2024-08-05 upd img
2024-08-05 add link to img
2024-08-05 link to root
2024-08-06 add license
2024-08-09 rename license
2024-08-09 add license to readme
2024-08-11 license period
2025-03-31 I also publish here the digitally controlled linear power supply already present on my website - Pubblico qui anche l'alimentatore lineare a controllo digitale già presente sul mio sito web
2025-03-31 Add LinearPS screenshot
2025-04-02 fix warning signed-unsigned
2025-04-04 first readme.md
2025-04-05 Value of R49 changed to 330K ohms because with transformers with slightly higher voltage the current limiter had difficulty lowering the output voltage
2025-04-06 I change the mode for self-oscillation prevention by increasing the capacitance of C18 which now works as both integrator/low-pass. Firmware fixed too
2025-04-07 Fixed PCB errors. Replace C19 and added R51 to prevent self-oscillations
2025-04-07 C19 and R51 removed
2025-04-07 title
2025-04-08 C22 reverted for improve and/or personalize self-oscillations immunity. Added parametric Freecad electronic enclosure
2025-04-08 Added R51
2025-04-08 Update analog version
2025-04-10 Fix link and enclosure
2025-04-11 max voltage limited
2025-04-13 add clarification
2025-05-02 update notes
2025-05-05 first PRESSFLOWino commit
2025-05-05 first PRESSFLOWino fix
2025-05-05 improve PRESSFLOWino README
2025-05-05 add PRESSFLOWino pic
2025-05-05 main page: add PRESSFLOWino
2025-05-05 add Air Oil Filter as flow switch
2025-05-05 add 3mf files
2025-05-07 removed some defects on the flow filter-detector design
2025-05-10 add connecting spacer, review filter
2025-05-10 Connecting Spacer updated
2025-05-22 panel picture
2025-05-23 added long press on Enter button and flux control in pump mode
2025-05-29 DigitalLinearPowerSupply: added C19 (snubber)
2025-07-23 Firmware: add lcd.clear every 1 sec
2025-07-26 Firmware: update version
2026-02-03 decrease debounce delay to prevent invert direction
2026-02-22 clear ignore
